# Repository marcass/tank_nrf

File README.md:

# tank_nrf
Arduino, NRF and ultrasonic sensors

Resources:
* http://tmrh20.github.io/RF24Mesh/
* http://www.mysensors.org/
* https://bitbucket.org/teckel12/arduino-new-ping/wiki/Home
* http://www.gammon.com.au/forum/?id=12821 this is paowering using a capacitor/solar panel

Hardware:
* http://www.aliexpress.com/item/SINMAX-8dBi-Wifi-Antenna-IEEE-802-11b-g-Indoor-Parabolic-Antenna-2-4GHz-High-Gain-USB/848558663.html?spm=2114.01020208.3.10.mWn7eg&ws_ab_test=searchweb201556_6,searchweb201644_3_79_78_77_82_80_62,searchweb201560_5
* nrf modules like NRF24L01+PA+LNA
* http://www.aliexpress.com/item/J34-Free-Shipping-DC-5V-Ultrasonic-Module-Distance-Measuring-Transducer-Sensor-Perfect-Waterproof/32400424410.html?spm=2114.01020208.3.1.lSEPYa&ws_ab_test=searchweb201556_6,searchweb201644_3_79_78_77_82_80_62,searchweb201560_5

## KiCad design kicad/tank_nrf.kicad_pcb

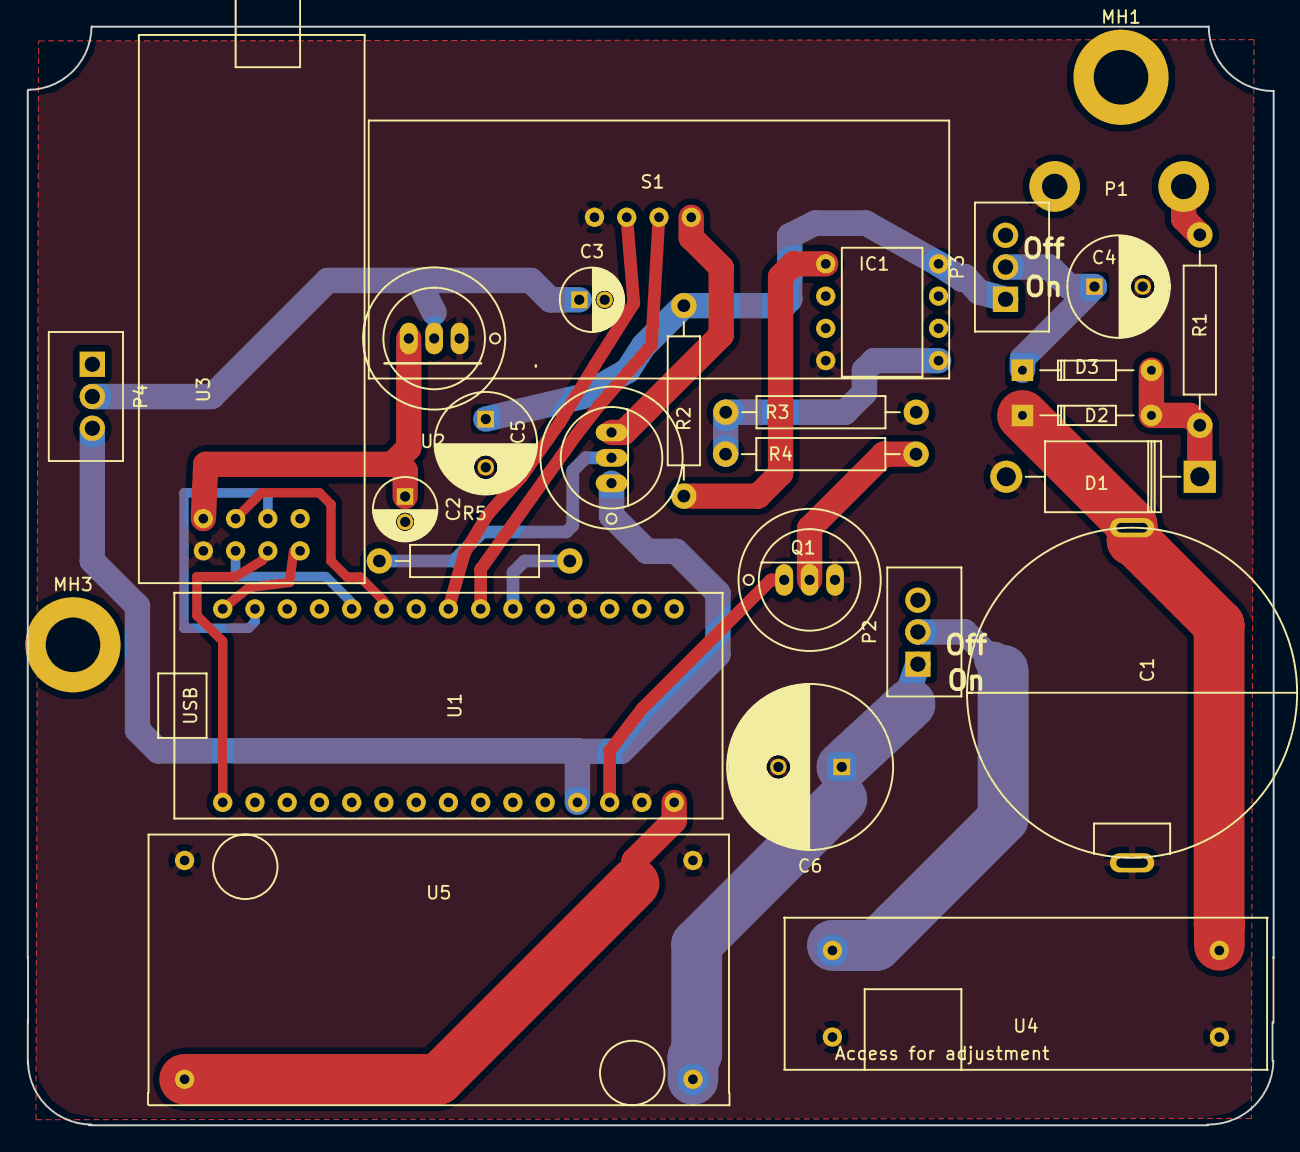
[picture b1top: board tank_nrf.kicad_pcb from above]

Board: 2 copper layers, 98.1 x 86.6 mm, 29 parts (0 on the bottom side), 26 nets.

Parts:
C1: 4F; 4FCap
C2, C3: 1muF; C_Radial_D5_L11_P2
C4: 440muF; C_Radial_D8_L21_P3.8
C5: 440uF; C_Radial_D8_L13_P3.8
C6: 2F; C_Radial_D13_L21_P5
D1: 1N5817 (prev IN752); Diode_DO-201AD_Horizontal_RM15
D2, D3: IN4148; Diode_DO-35_SOD27_Horizontal_RM10
IC1: ATTINY25-SS; ATTiny85
MH1, MH3: CONN_01X01; MountingHole_4.3mm_M4_DIN965_Pad
P1: CONN_01X02; WireConnection_2.00mmDrill
P2: Jumper1; Wafer_Vertical10x5.8x7RM2.5-3
P3: Jumper2; Wafer_Vertical10x5.8x7RM2.5-3
P4: Jumper3; Wafer_Vertical10x5.8x7RM2.5-3
Q1: 2N7000
Q3: PN2222A; OldSowjetaera_Transistor_Type-I_BigPads
R1: 220; Resistor_Horizontal_RM15mm
R2, R3: 10k; Resistor_Horizontal_RM15mm
R4: 150; Resistor_Horizontal_RM15mm
R5: 470; Resistor_Horizontal_RM15mm
S1: JSN-SR40T; JSN-SR04T
U1: arduino_nano (mini?); ArduinoNano
U2: MCP1700T-3002E/TT; OldSowjetaera_Transistor_Type-I_BigPads
U3: nRF24L01+; nrf
U4: MT3608b; MT3608
U5: LM2596b; LM2596

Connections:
+5V: P4.3, Q3.1, U1.12
ATtiny5V: C5.1, IC1.8, P3.1, R2.2
CE: U1.26, U3.3
CS: U1.25, U3.4
Echo: S1.3, U1.23
GND: C1.2, C2.2, C3.2, C4.2, C5.2, C6.2, D1.2, IC1.4, P1.1, Q1.2, R3.2, S1.4, U1.14, U1.19, U2.1, U3.1, U4.2, U4.3, U5.2, U5.3
LM2596+: U1.15, U5.4
MISO: U1.30, U3.7
MOSI: U1.29, U3.6
NanoReset: Q1.3, U1.13
unnamed: C2.1, U2.3, U3.2
unnamed: C3.1, P4.2, U2.2
unnamed: C4.1, D3.1, P3.2
unnamed: C6.1, P2.1, U5.1
unnamed: D1.1, D2.2, D3.2, R1.2
unnamed: IC1.1, R2.1
unnamed: IC1.5, R3.1, R4.2
unnamed: P2.2, U4.4
unnamed: Q1.1, R4.1
unnamed: Q3.2, R5.1
unnamed: Q3.3, S1.1
SCK: U1.1, U3.5
Trig: S1.2, U1.22
echo_trans: R5.2, U1.21
solarpanel+: P1.2, R1.1
stepupmt3608+: C1.1, D2.1, U4.1

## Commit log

2015-12-20 Update README.md
    Fleshing out
2015-12-20 Update README.md
    nrf dexcription update
2015-12-20 Update README.md
    Update for water proof transceiver
2015-12-21 Update README.md
    Power options
2016-11-02 added brownout control courtesy of nick gammon
2016-12-05 optimise for powering up pin when u/s module needed
2016-12-06 started changeing sleep modes in line with new library
2016-12-07 Altered for sleep funciton in new rf lib
2017-05-31 added kicad, started on setup
2017-06-01 tideied up and have working mycontroller
